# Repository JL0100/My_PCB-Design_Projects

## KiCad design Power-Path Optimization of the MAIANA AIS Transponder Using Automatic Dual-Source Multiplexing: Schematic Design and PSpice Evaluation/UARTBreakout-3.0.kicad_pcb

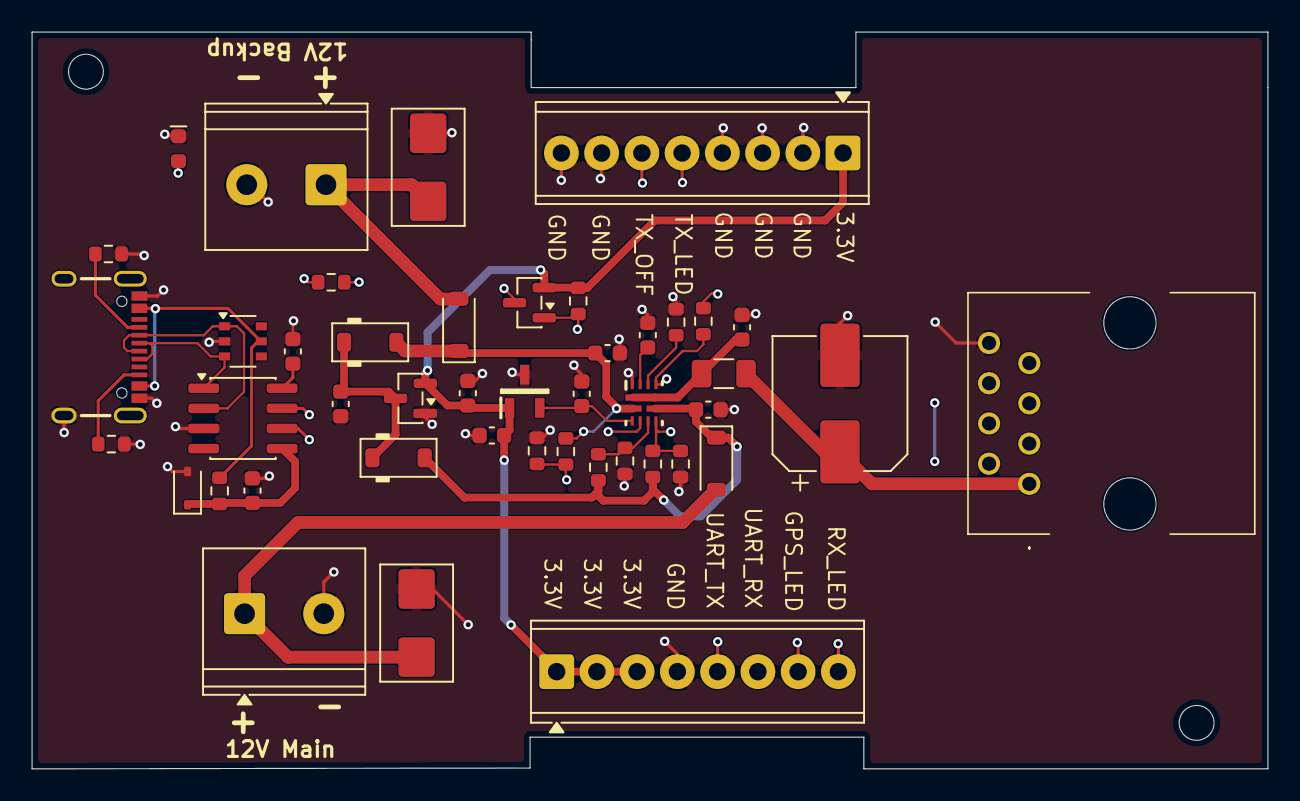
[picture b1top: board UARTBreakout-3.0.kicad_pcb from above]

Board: 4 copper layers, 78.0 x 46.5 mm, 45 parts (0 on the bottom side), 31 nets.

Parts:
C1, C3, C6, C7, C8, C13: 1uF; C_0603_1608Metric
C2, C9: 10uF; C_0603_1608Metric
C4, C5: 100nF; C_0603_1608Metric
C12: 100uF 25V; CP_Elec_8x6.2
D1, D4: SMBJ14CA; D_SMB_TVS
D2, D5: WSB5508L-2/TR; D_SOD-123
D3: MMSZ5226BS; D_SOD-323
D6, D7: 1N4148W-HE3-18; D_SOD-123
D8: Red; LED_0603_1608Metric_Red
F1: BSMD1206-050-16V; Fuse_1206_3216Metric
J1: USB_C_Receptacle; USB-C_16
J2: 955012821; RJ45_Molex_955012821
J5_MAIN1, J6__BACKUP1: Screw_Terminal_2_P5.00mm; TerminalBlock_Phoenix_PT-1,5-2-5.0-H_1x02_P5.00mm_Horizontal
JP2, JP3: M08SILK_FEMALE_PTH; TerminalBlock_Phoenix_MPT-0,5-8-2.54_1x08_P2.54mm_Horizontal
Q1: AO3401A; SOT-23
R1: 11k; R_0603_1608Metric
R2: 3.24k; R_0603_1608Metric
R3: 1Meg; R_0603_1608Metric
R4, R6: 57.6k; R_0603_1608Metric
R5, R7: 5k; R_0603_1608Metric
R8: 75; R_0603_1608Metric
R9: 80k; R_0603_1608Metric
R10: 10k; R_0603_1608Metric
R11: 1k; R_0603_1608Metric
R12, R13: 5.1k; R_0603_1608Metric
U1: SE8533X2-HF; SOT-23
U2: TPS2121RUXR; RUX0012A
U3: REF3325AIDBZR; SOT95P237X112-3N
U4: SRV05-4MR6T1G; TSOP-6_1.65x3.05mm_P0.95mm
U5: CH340N; SOIC-8_3.9x4.9mm_P1.27mm

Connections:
2.5V_XREF: C9.1, U2.3 (CP2), U3.2 (OUT)
3.3V: C2.1, C8.1, JP2.1, JP2.2, JP2.3, JP3.1, Q1.2 (S), R10.1, U1.2 (VO), U3.1 (IN)
AUX_VOLTAGE: C1.1, D6.1 (K), D7.1 (K), U1.3 (VIN)
BACKUP_PWR_12V: D4.2 (A), D5.2 (Anode), J6__BACKUP1.1
D+: J1.A6 (D+), J1.B6 (D+), U4.3 (IO2), U5.1 (D+)
D-: J1.A7 (D-), J1.B7 (D-), U4.1 (IO1), U5.2 (D-)
GND: C1.2, C2.2, C3.2, C4.2, C5.2, C6.2, C7.2, C8.2, C9.2, C12.2, C13.2, D1.1 (K), D3.2 (Anode), D4.1 (K), D8.1 (K), J1.GND, J1.S (SHIELD), J2.8, J5_MAIN1.2, J6__BACKUP1.2, JP2.4, JP3.2, JP3.3, JP3.4, JP3.7, JP3.8, R2.2, R5.2, R7.2, R9.2, R12.2, R13.2, U1.1 (GND), U2.12 (GND), U3.3 (GND), U4.2 (GND), U5.3 (GND)
GPS_LED: J2.4, JP2.7
MAIN_PWR_12V: D1.2 (A), D2.2 (Anode), J5_MAIN1.1
unnamed: C13.1, F1.1, U2.1 (OUT), U2.8 (OUT)
unnamed: C6.1, D2.1 (Cathode), D6.2 (A), R1.1, R4.1, U2.7 (IN1)
unnamed: C7.1, D5.1 (Cathode), D7.2 (A), R6.1, U2.2 (IN2)
unnamed: D8.2 (A), R11.2
unnamed: J1.A5 (CC1), R12.1
unnamed: J1.B5 (CC2), R13.1
unnamed: Q1.3 (D), R11.1
unnamed: R9.1, U2.10 (ILM)
unnamed: R6.2, R7.1, U2.4 (OV2)
unnamed: R1.2, R2.1, R3.1, U2.6 (PR1)
unnamed: C3.1, U2.11 (SS)
unnamed: C4.1, U5.8 (V3)
OV1: R4.2, R5.1, U2.5 (OV1)
PMUX_STATUS: Q1.1 (G), R3.2, R10.2, U2.9 (ST)
RX_LED: J2.6, JP2.8
TRANSPONDER_UART_RX: J2.3, JP2.6, U5.6 (TX)
TRANSPONDER_UART_TX: J2.5, JP2.5, U5.7 (RX)
TX_LED: J2.7, JP3.6
TX_OFF: J2.2, JP3.5
USB_3V3: C5.1, D3.1 (Cathode), R8.2, U5.5 (VCC)
VBUS: J1.VBUS, R8.1, U4.5 (VCC)
V_OUT: C12.1, F1.2, J2.1

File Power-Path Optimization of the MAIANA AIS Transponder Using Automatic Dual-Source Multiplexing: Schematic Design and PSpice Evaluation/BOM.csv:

"Reference","Qty","Value","Footprint","Datasheet","Manufacturer_Name","Manufacturer_Part_Number","Mouser Part Number","PACKAGE","PARTNO","DIGIKEY-PURCHASE-URL","ARROW_ELECTRONICS-PURCHASE-URL","MANUFACTURER","LCSC"
"C1,C3,C6,C7,C8,C13","6","1uF","Capacitor_SMD:C_0603_1608Metric","https://jlcpcb.com/partdetail/16531-CL10A105KB8NNNC/C15849","","","","","","","","","C15849"
"C2,C9","2","10uF","Capacitor_SMD:C_0603_1608Metric","https://jlcpcb.com/partdetail/97651-CL10A106MA8NRNC/C96446","","","","","","","","","C96446"
"C4,C5","2","100nF","Capacitor_SMD:C_0603_1608Metric","https://jlcpcb.com/partdetail/YAGEO-CC0603KRX5R8BB104/C2930551","","","","","","","","","C2930551"
"C12","1","100uF 25V","Capacitor_SMD:CP_Elec_8x6.2","https://industrial.panasonic.com/cdbs/www-data/pdf/RDE0000/A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","","","","","","","","Panasonic","C178539"
"D1,D4","2","SMBJ14CA","PCM_Diode_SMD_AKL:D_SMB_TVS","https://www.tme.eu/Document/0b6222bec7e12d83185b51d73cb6a54d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","","","","","","","","","C9020"
"D2,D5","2","WSB5508L-2/TR","Diode_SMD:D_SOD-123","https://www.lcsc.com/datasheet/C239542.pdf","","","","","WSB5508L-2/TR","","","","C239542"
"D3","1","MMSZ5226BS","Diode_SMD:D_SOD-323","https://jlcpcb.com/partdetail/DiodesIncorporated-MMSZ5226BS_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","","","","","","","","","C145097"
"D6,D7","2","1N4148W-HE3-18","PCM_Diode_SMD_AKL:D_SOD-123","https://datasheet.octopart.com/1N4148W-HE3-18-Vishay-datashe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","","","","","","","","","C191428"
"D8","1","Red","PCM_SparkFun-LED:LED_0603_1608Metric_Red","https://www.kingbrightusa.com/images/catalog/SPEC/APT1608SURCK.pdf","","","","","","","","",""
"F1","1","BSMD1206-050-16V","Fuse:Fuse_1206_3216Metric","","","","","","BSMD1206-050-16V","","","",""
"J1","1","USB_C_Receptacle","PCM_SparkFun-Connector:USB-C_16","https://www.usb.org/sites/default/files/documents/usb_type-c.zip","","","","","","","","",""
"J2","1","955012821","Connector_RJ:RJ45_Molex_955012821","https://www.mouser.ph/en/ProductDetail/Molex/95501-2821?qs=L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","","","","","955012821","","","","C19800963"
"J5_MAIN1,J6__BACKUP1","2","Screw_Terminal_2_P5.00mm","TerminalBlock_Phoenix:TerminalBlock_Phoenix_PT-1,5-2-5.0-H_1x02_P5.00mm_Horizontal","","","","","","","","","",""
"JP2,JP3","2","M08SILK_FEMALE_PTH","TerminalBlock_Phoenix:TerminalBlock_Phoenix_MPT-0,5-8-2.54_1x08_P2.54mm_Horizontal","","","","","","","","","",""
"Q1","1","AO3401A","Package_TO_SOT_SMD:SOT-23","http://www.aosmd.com/pdfs/datasheet/AO3401A.pdf","","","","","","","","","C15127"
"R1","1","11k","Resistor_SMD:R_0603_1608Metric","","","","","","","","","",""
"R2","1","3.24k","Resistor_SMD:R_0603_1608Metric","","","","","","","","","",""
"R3","1","1Meg","Resistor_SMD:R_0603_1608Metric","","","","","","","","","",""
"R4,R6","2","57.6k","Resistor_SMD:R_0603_1608Metric","","","","","","","","","",""
"R5,R7","2","5k","Resistor_SMD:R_0603_1608Metric","","","","","","","","","",""
"R8","1","75","Resistor_SMD:R_0603_1608Metric","","","","","","","","","",""
"R9","1","80k","Resistor_SMD:R_0603_1608Metric","","","","","","","","","",""
"R10","1","10k","Resistor_SMD:R_0603_1608Metric","","","","","","","","","",""
"R11","1","1k","Resistor_SMD:R_0603_1608Metric","","","","","","","","","",""
"R12,R13","2","5.1k","Resistor_SMD:R_0603_1608Metric","","","","","","","","","",""
"TP1,TP2,TP3,TP4,TP5,TP6,TP7,TP8,TP9,TP11,TP12,TP13,TP14,TP15,TP19,TP20","16","TestPoint","","","","","","","","","","",""
"U1","1","SE8533X2-HF","Package_TO_SOT_SMD:SOT-23","https://xonstorage.z8.web.core.windows.net/pdf/seaward_se853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","","","","","C115016","","","",""
"U2","1","TPS2121RUXR","TPS2121:RUX0012A","https://www.ti.com/lit/gpn/tps2121","","","","","","","","",""
"U3","1","REF3325AIDBZR","REF3325AIDBZR:SOT95P237X112-3N","https://www.ti.com/lit/ds/symlink/ref33.pdf?ts=1791040549910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","","","","","","","","",""
"U4","1","SRV05-4MR6T1G","Package_SO:TSOP-6_1.65x3.05mm_P0.95mm","https://jlcpcb.com/partdetail/onsemi-SRV054MR6T1G/C604719","","","","","","","","","C604719"
"U5","1","CH340N","Package_SO:SOIC-8_3.9x4.9mm_P1.27mm","https://jlcpcb.com/partdetail/WCH_Jiangsu_Qin_Heng-CH340N/C2977777","","","","","CH340N","","","","C2977777"

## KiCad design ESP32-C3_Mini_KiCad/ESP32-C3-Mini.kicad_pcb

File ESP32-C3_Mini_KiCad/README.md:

# ESP32-C3 Mini Evaluation Board in KiCad 10

A custom PCB design for the **ESP32-C3 Mini** microcontroller created in KiCad 10

## Project Overview

This project is a clean, minimal development board created by following the [
KiCad 9 ESP32-C3 Mini PCB Design | Full Schematic Walkthrough] from https://www.youtube.com/watch?v=-iZbwzr0dS8

It uses a hierarchical schematic structure to separate the system block diagram from the detailed power, microcontroller, and I/O circuitry.

## Hardware Specifications
* **Microcontroller:** `ESP32-C3-WROOM-02` (integrates Wi-Fi, flash memory, RF components, and an internal 40 MHz system crystal)
* **USB-C Input & Protection:** 
  * 16-pin USB 2.0 Type-C receptacle configured as a 5V power sink using `5.1 kΩ` pull-down resistors on `CC1` and `CC2`
  * Native USB 2.0 differential data lines (`IO18` / `IO19`) protected by a `USBLC6` low-capacitance ESD protection array
  * `VBUS` 5V line protected by a unidirectional PES-series ESD diode and a Pi-filter stage (`4.7 µF` capacitors with a `0 Ω` placeholder resistor)
* **Voltage Regulation:** `AP2112` 3.3V LDO linear regulator (600 mA output) with `4.7 µF` input/output decoupling capacitors
* **External RTC Clock:** `32.768 kHz` (`ABS07` series) low-speed crystal with load capacitors and a feedback resistor connected to `IO0` and `IO1` for real-time clock and low-power operation
* **Boot & Reset Controls:**
  * Manual **Reset** push-button on the `EN` pin with a `10 kΩ` pull-up resistor and RC debounce filter (`100 Ω` + `100 nF`)
  * Manual **Boot** push-button on strapping pin `IO9` (`10 kΩ` pull-up) to enter firmware download mode
  * Dedicated `10 kΩ` pull-up resistors on strapping pins `IO2` and `IO8` for reliable SPI flash booting
* **Expansion Headers:** Dual 8-pin (`2.54 mm` pitch) headers exposing `3.3V`, `GND`, `UART`, `JTAG`, and general-purpose GPIOs in physical module pin order

## Repository Contents
* **`ESP32-C3-Mini.kicad_pro`** – Main KiCad 9 project file
* **`ESP32-C3-Mini.kicad_sch`** – Root schematic sheet
* **`BlockDiagram.kicad_sch`** – High-level system block diagram
* **`ESP32C3Mini.kicad_sch`** – Detailed hierarchical schematic sub-sheet
* **`ESP32-C3-Mini.kicad_pcb`** – PCB layout file
* **`ESP32-C3-Mini.png`** – Board schematic/layout preview

## Acknowledgements
* Design based on the tutorial by **PCB Learning Collective**: [KiCad 9 ESP32-C3 Mini PCB Design | Full Schematic Walkthrough] (https://www.youtube.com/watch?v=-iZbwzr0dS8)

## License
This project is licensed under the terms of the [LICENSE](../LICENSE) file in the root directory.

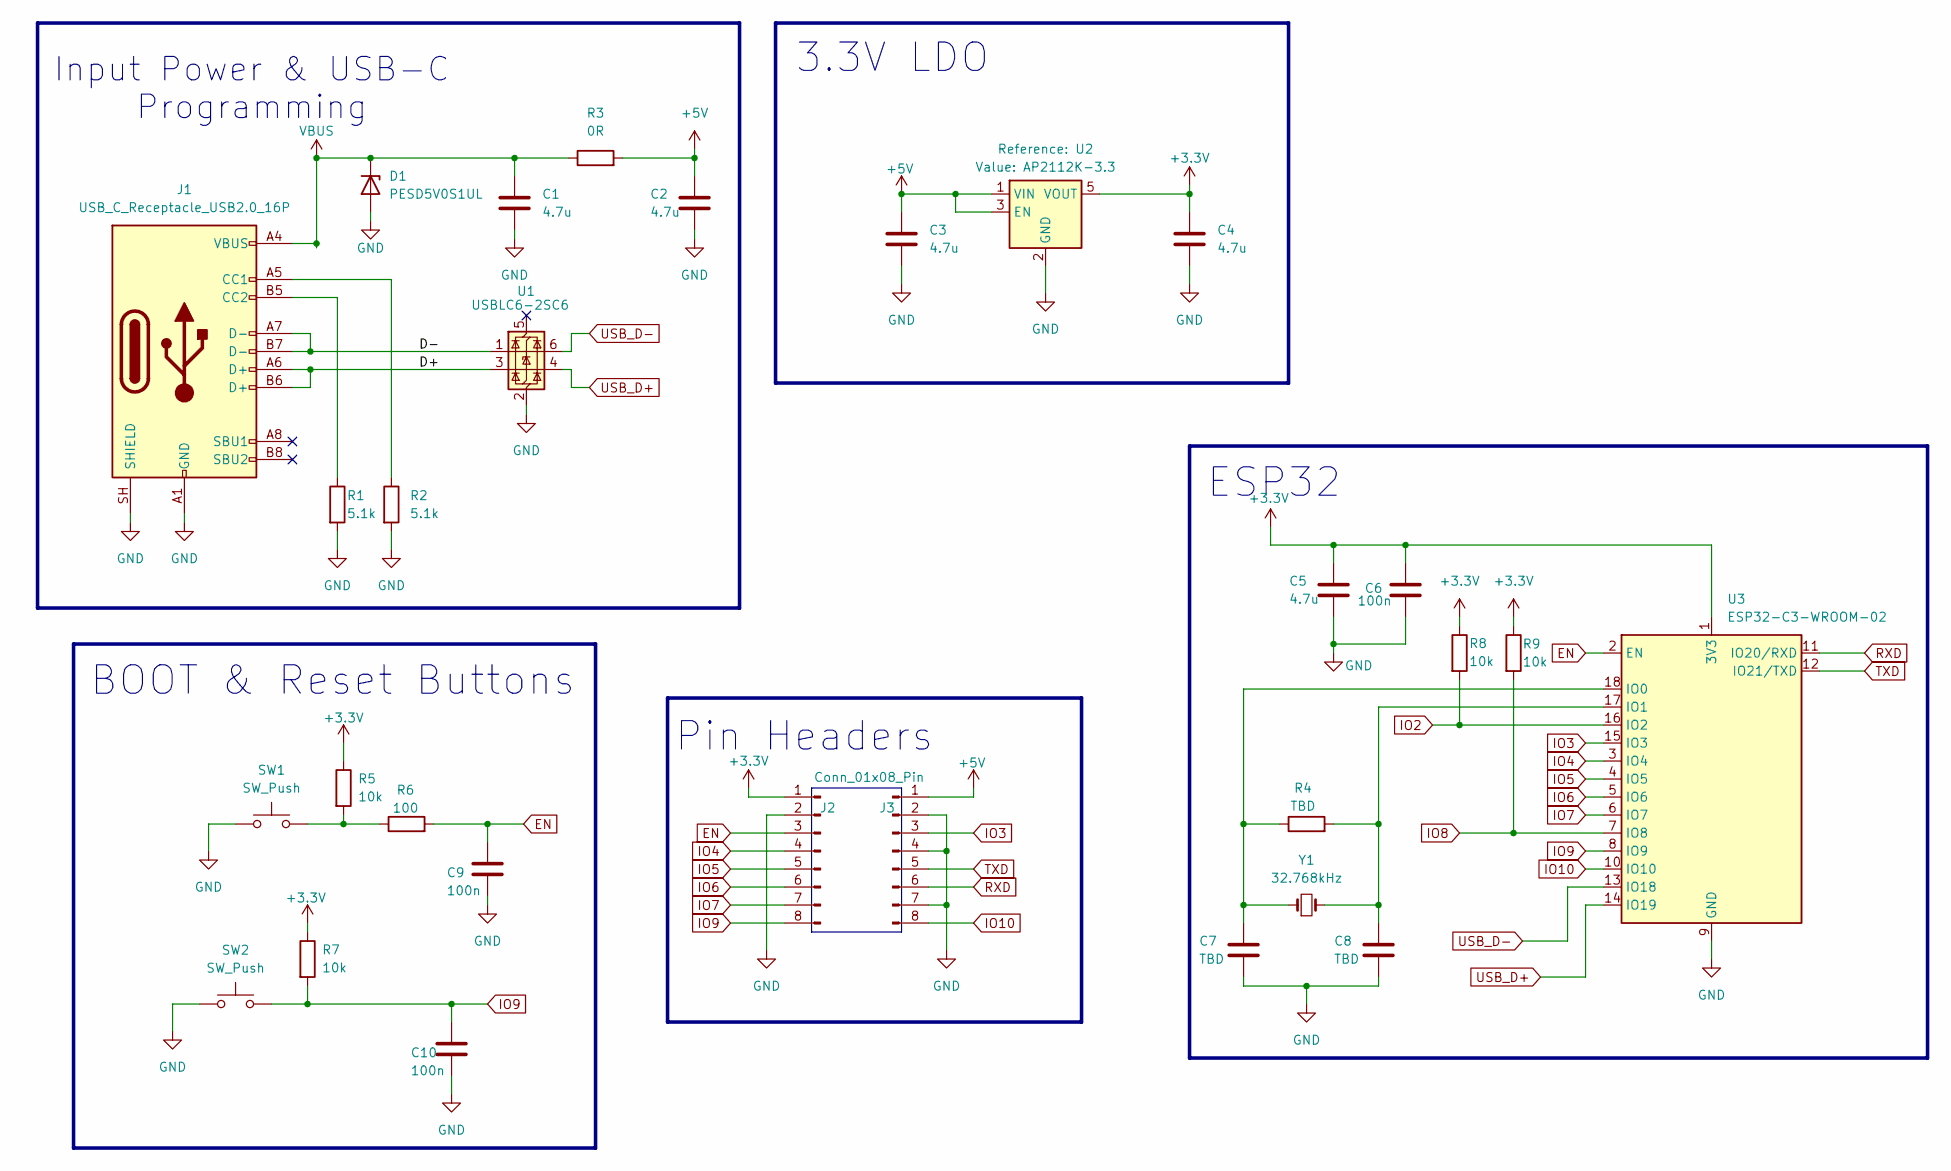
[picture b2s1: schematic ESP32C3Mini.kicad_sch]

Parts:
C1, C2, C3, C4, C5: 4.7u; C_0805_2012Metric
C6, C9, C10: 100n; C_0402_1005Metric
C7, C8: TBD; C_0402_1005Metric
D1: PESD5V0S1UL; D_SOD-882
J1: USB_C_Receptacle_USB2.0_16P; USB_C_Receptacle_G-Switch_GT-USB-7010ASV
J2, J3: Conn_01x08_Pin; PinHeader_1x08_P2.54mm_Vertical
R1, R2: 5.1k; R_0402_1005Metric
R3: 0R; R_0805_2012Metric
R4: TBD; R_0201_0603Metric
R5, R7, R8, R9: 10k; R_0402_1005Metric
R6: 100; R_0402_1005Metric
SW1, SW2: SW_Push; SW_SPST_B3U-1000P
U1: USBLC6-2SC6; SOT-23-6
U2: AP2112K-3.3; SOT23-5
U3: ESP32-C3-WROOM-02
Y1: 32.768kHz; Crystal_SMD_3215-2Pin_3.2x1.5mm

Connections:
+3.3V: C4.1, C5.1, C6.1, J2.1, R5.1, R7.1, R8.1, R9.1, U2.5 (VOUT), U3.1 (3V3)
+5V: C2.1, C3.1, J3.1, R3.2, U2.1 (VIN), U2.3 (EN)
/ESP32-C3-Mini/D+: J1.A6 (D+), J1.B6 (D+), U1.3 (I/O2)
/ESP32-C3-Mini/D-: J1.A7 (D-), J1.B7 (D-), U1.1 (I/O1)
EN: C9.1, J2.3, R6.2, U3.2 (EN)
GND: C1.2, C2.2, C3.2, C4.2, C5.2, C6.2, C7.2, C8.2, C9.2, C10.2, D1.2 (A), J1.A1 (GND), J1.A12 (GND), J1.B1 (GND), J1.B12 (GND), J1.SH (SHIELD), J2.2, J3.2, J3.4, J3.7, R1.2, R2.2, SW1.1, SW2.1, U1.2 (GND), U2.2 (GND), U3.9 (GND), U3.19 (GND); also elsewhere on the board
IO2: R8.2, U3.16 (IO2)
IO3: J3.3, U3.15 (IO3)
IO4: J2.4, U3.3 (IO4)
IO5: J2.5, U3.4 (IO5)
IO6: J2.6, U3.5 (IO6)
IO7: J2.7, U3.6 (IO7)
IO8: R9.2, U3.7 (IO8)
IO9: C10.1, J2.8, R7.2, SW2.2, U3.8 (IO9); also elsewhere on the board
IO10: J3.8, U3.10 (IO10)
unnamed: J1.A5 (CC1), R2.1
unnamed: J1.B5 (CC2), R1.1
unnamed 17: R5.2, R6.1, SW1.2; also elsewhere on the board
unnamed: C7.1, R4.1, U3.18 (IO0), Y1.1
unnamed: C8.1, R4.2, U3.17 (IO1), Y1.2
RXD: J3.6, U3.11 (IO20/RXD)
TXD: J3.5, U3.12 (IO21/TXD)
USB_D+: U1.4 (I/O2), U3.14 (IO19)
USB_D-: U1.6 (I/O1), U3.13 (IO18)
VBUS: C1.1, D1.1 (K), J1.A4 (VBUS), J1.A9 (VBUS), J1.B4 (VBUS), J1.B9 (VBUS), R3.1

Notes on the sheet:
ESP32
BOOT & Reset Buttons
Input Power & USB-C Programming
Pin Headers
3.3V LDO

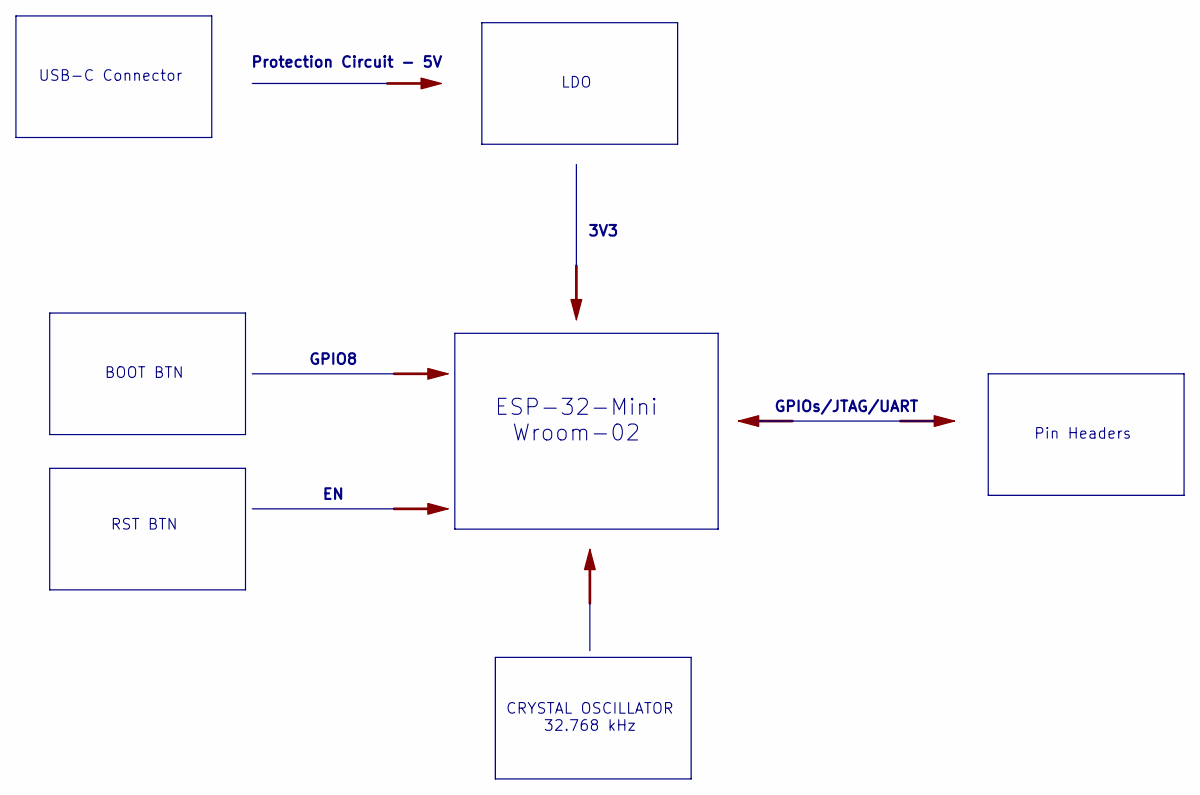
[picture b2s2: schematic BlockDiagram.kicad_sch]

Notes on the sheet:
GPIO8
Protection Circuit - 5V
GPIOs/JTAG/UART
RST BTN
USB-C Connector
Pin Headers
CRYSTAL OSCILLATOR 32.768 kHz
3V3
BOOT BTN
ESP-32-Mini Wroom-02
LDO

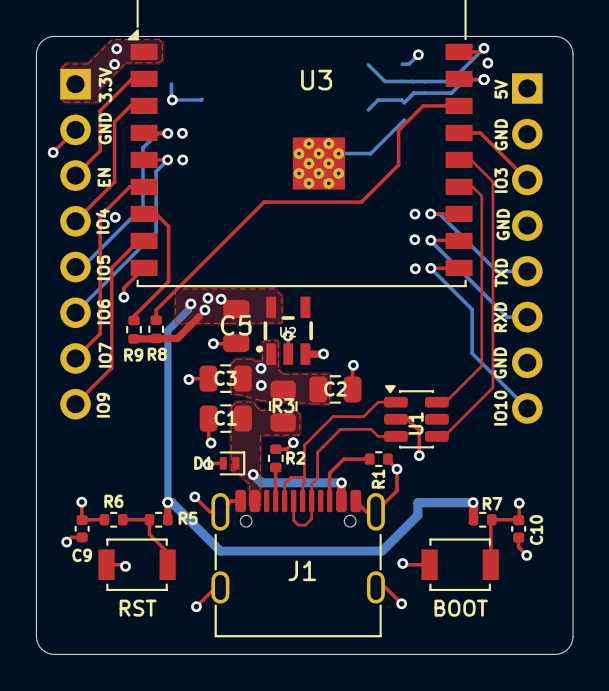
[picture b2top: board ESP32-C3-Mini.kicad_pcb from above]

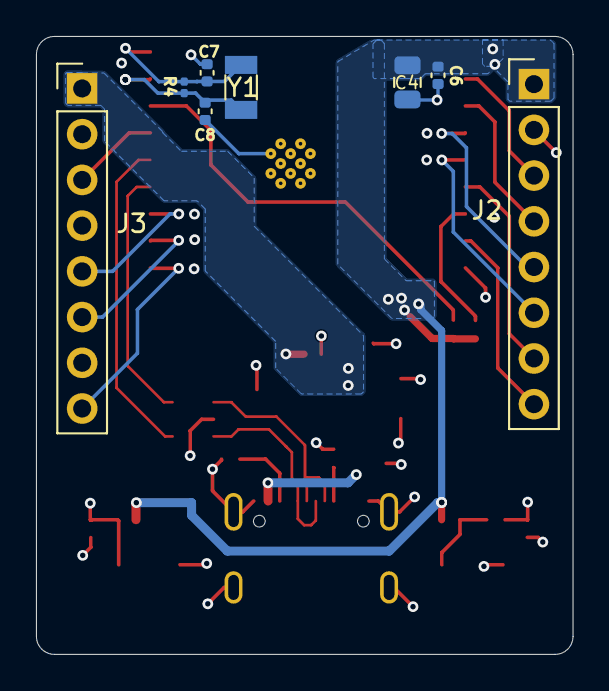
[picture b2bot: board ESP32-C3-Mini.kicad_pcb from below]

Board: 4 copper layers, 29.8 x 34.3 mm, 29 parts (8 on the bottom side), 25 nets.

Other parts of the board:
BOOT: SW_Push; SW_SPST_B3U-1000P
RST: SW_Push; SW_SPST_B3U-1000P

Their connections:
GND: BOOT.1, RST.1; also elsewhere on the board
IO9: BOOT.2; also elsewhere on the board
unnamed 17: RST.2; also elsewhere on the board
